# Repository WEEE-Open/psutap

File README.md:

# PSUtap
The PSUtap is a battery powered device designed to sit between the PSU (power supply unit) and the motherboard of a desktop computer.  
It's purpose is to constantly monitor the power lines (voltage and current) to detect power related issues: short circuits, open circuits, overloads, overvoltages, etc...   
It taps the lines from the main 24 pin ATX connector and the lines from another 4 pin connector to monitor:
* 12V1
* 12V2
* 5V
* 5VSB
* 3V3

## Structure of the device
The device is divided into three different boards, which are mounted on top of each other. From the bottom up, they are:
* the analog board
* the digital board
* the screen module  

The three are connected through male/female headers and communicate through an SPI interface.

## Analog board
This board gets its name from the fact that it has current sensing ICs, voltage sensing voltage dividers and an ADC to transmit the data to the digital board.  
For the current sensing, we've used some [LT6105](https://www.analog.com/media/en/technical-documentation/data-sheets/6105fa.pdf) ICs, which are essentially (differential) voltage controlled current sources. The configuration in our board is not much different than the typical application shown in the schematic.  
For the voltage sensing, we've used some regular voltage dividers, with a bit of margin so that we can also detect overvoltages.  
The ADC is an [AD7708](https://www.analog.com/media/en/technical-documentation/data-sheets/AD7708_7718.pdf), which is a delta-sigma, 16 bits, 10 channels ADC with integrated SPI interface, which is why we chose it, so that we could easily connect it to a uC without using too many wires.

## Digital Board
This board contains the uC, the brain of the entire device, a [CH340G](https://cdn.sparkfun.com/datasheets/Dev/Arduino/Other/CH340DS1.PDF) USB to serial converter,  the battery charging and protection circuit, a USB port and some buttons for the user input.  
The used uC is an [ATmega328P](https://ww1.microchip.com/downloads/en/DeviceDoc/Atmel-7810-Automotive-Microcontrollers-ATmega328P_Datasheet.pdf), which will be flashed with the Arduino bootloader so that it can be easily programmed through the Arduino IDE.  
Its main tasks are:
* reading the data coming from the ADC
* displaying on the screen
* handling user inputs
* interact with the computer through the USB port (data logging/remote control)

## Screen module
The screen module is a 240x320 2.8'' LCD, and the serial number is `tjctm24028-spi`.  
It's purpose is to show the user all the measured voltages and currents at once, so that a problem related with the power lines can be located very quickly, and also graph the voltages and currents wrt time.

## Current state
* The schematic for the analog and the digital board have been finished
* The PCB of the first board has to be redesigned completly
* The PCB of the second board has to be designed from scratch
* All the software for the microcontroller has to be written
* Testing (a lot of testing)

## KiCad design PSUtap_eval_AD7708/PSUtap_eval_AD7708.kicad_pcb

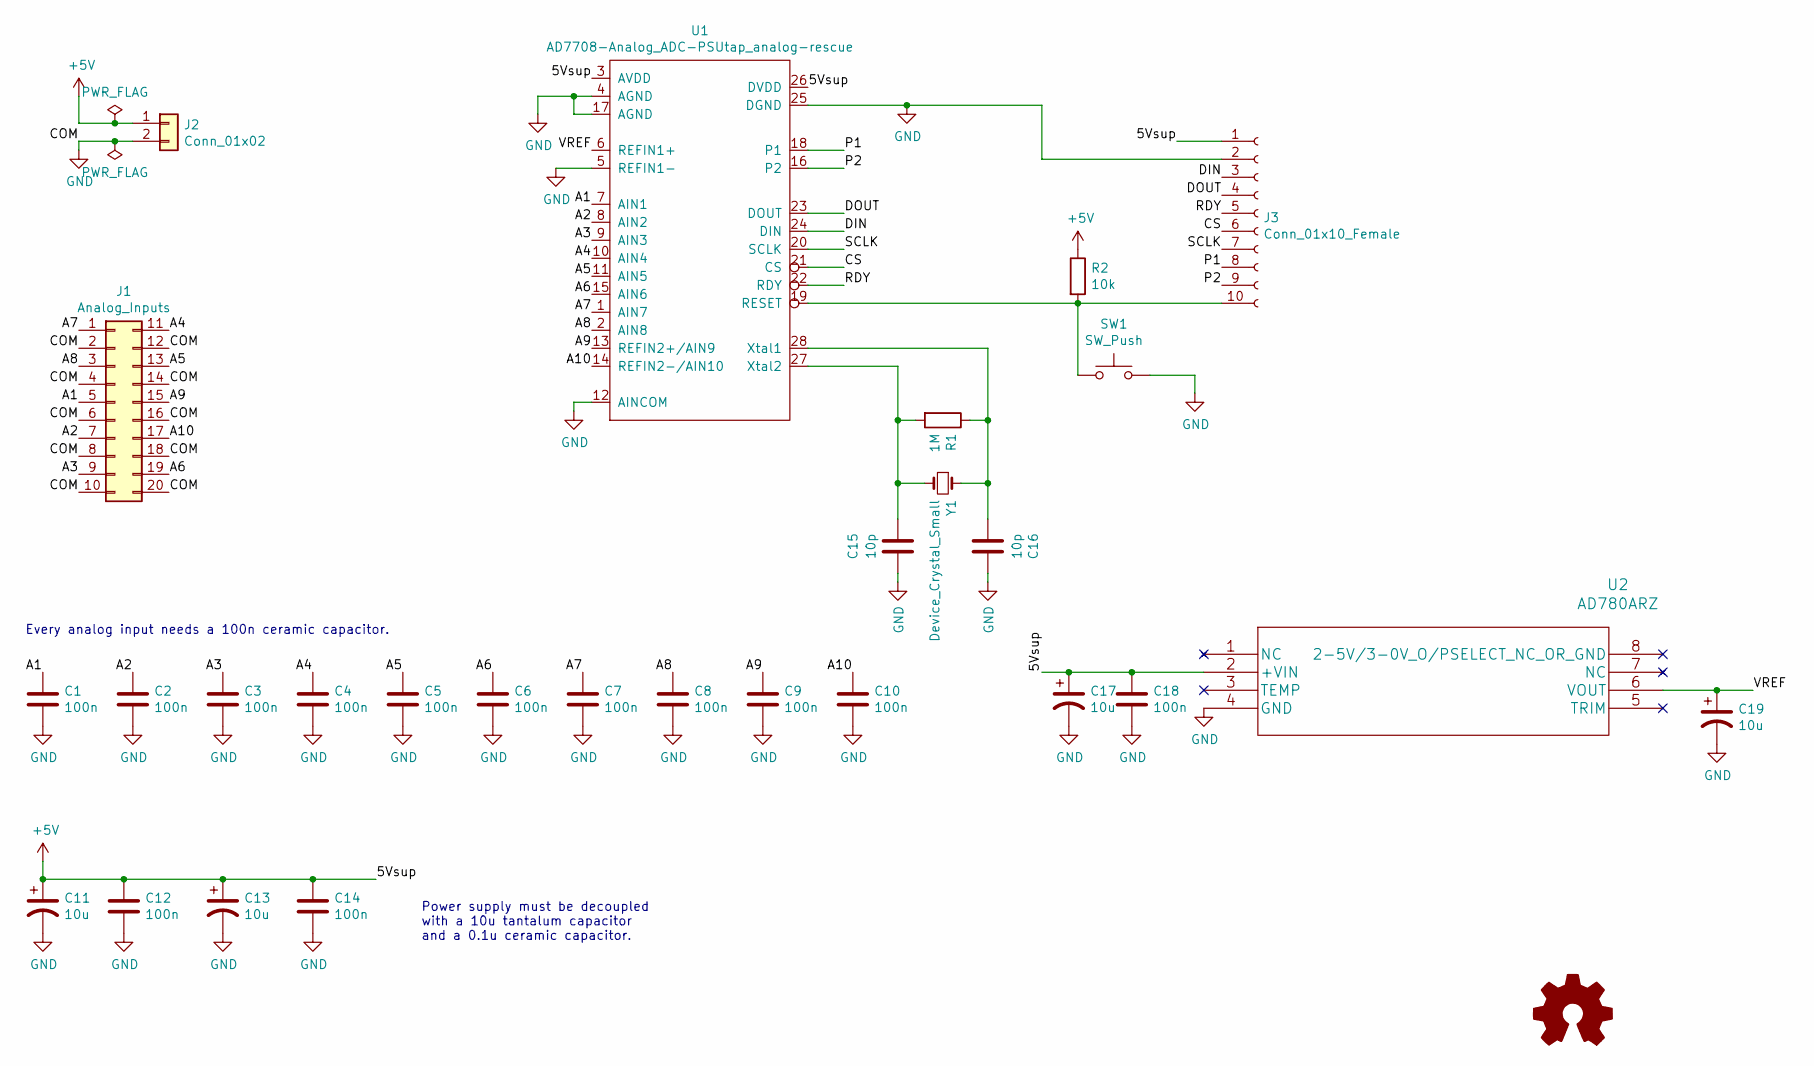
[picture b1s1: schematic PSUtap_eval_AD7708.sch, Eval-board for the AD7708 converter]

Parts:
C1, C2, C3, C4, C5, C6, C7, C8, C9, C10, C12, C14, C18: 100n; C_0603_1608Metric_Pad1.05x0.95mm_HandSolder
C11, C13, C17, C19: 10u; C_0805_2012Metric
C15, C16: 10p; C_0603_1608Metric_Pad1.05x0.95mm_HandSolder
J1: Analog_Inputs; PinSocket_2x10_P2.54mm_Vertical
J2: Conn_01x02; PinSocket_1x02_P2.54mm_Vertical
J3: Conn_01x10_Female; PinSocket_1x10_P2.54mm_Vertical
R1: 1M; R_0603_1608Metric_Pad1.05x0.95mm_HandSolder
R2: 10k; R_0603_1608Metric_Pad1.05x0.95mm_HandSolder
SW1: SW_Push; SW_SPST_B3U-1000P
U1: AD7708-Analog_ADC-PSUtap_analog-rescue; SOIC-28W_7.5x18.7mm_P1.27mm
U2: AD780ARZ; SSOP-8_3.9x5.05mm_P1.27mm
Y1: Device_Crystal_Small; Crystal_SMD_EuroQuartz_EQ161-2Pin_3.2x1.5mm_HandSoldering

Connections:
+5V: C11.1, C12.1, C13.1, C14.1, C17.1, C18.1, J2.1, J3.1, R2.1, U1.3 (AVDD), U1.26 (DVDD), U2.2 (+VIN)
/A1: C1.1, J1.5, U1.7 (AIN1)
/A2: C2.1, J1.7, U1.8 (AIN2)
/A3: C3.1, J1.9, U1.9 (AIN3)
/A4: C4.1, J1.11, U1.10 (AIN4)
/A5: C5.1, J1.13, U1.11 (AIN5)
/A6: C6.1, J1.19, U1.15 (AIN6)
/A7: C7.1, J1.1, U1.1 (AIN7)
/A8: C8.1, J1.3, U1.2 (AIN8)
/A9: C9.1, J1.15, U1.13 (REFIN2+/AIN9)
/A10: C10.1, J1.17, U1.14 (REFIN2-/AIN10)
/CS: J3.6, U1.21 (CS)
/DIN: J3.3, U1.24 (DIN)
/DOUT: J3.4, U1.23 (DOUT)
/P1: J3.8, U1.18 (P1)
/P2: J3.9, U1.16 (P2)
/RDY: J3.5, U1.22 (RDY)
/SCLK: J3.7, U1.20 (SCLK)
/VREF: C19.1, U1.6 (REFIN1+), U2.6 (VOUT); also elsewhere on the board
GND: C1.2, C2.2, C3.2, C4.2, C5.2, C6.2, C7.2, C8.2, C9.2, C10.2, C11.2, C12.2, C13.2, C14.2, C15.1, C16.1, C17.2, C18.2, C19.2, J1.2, J1.4, J1.6, J1.8, J1.10, J1.12, J1.14, J1.16, J1.18, J1.20, J2.2, J3.2, SW1.2, U1.4 (AGND), U1.5 (REFIN1-), U1.12 (AINCOM), U1.17 (AGND), U1.25 (DGND), U2.4 (GND)
unnamed: C15.2, R1.2, U1.27 (Xtal2), Y1.2
unnamed: C16.2, R1.1, U1.28 (Xtal1), Y1.1
unnamed: J3.10, R2.2, SW1.1, U1.19 (RESET)

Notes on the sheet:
Power supply must be decoupled with a 10u tantalum capacitor and a 0.1u ceramic capacitor.
Every analog input needs a 100n ceramic capacitor.

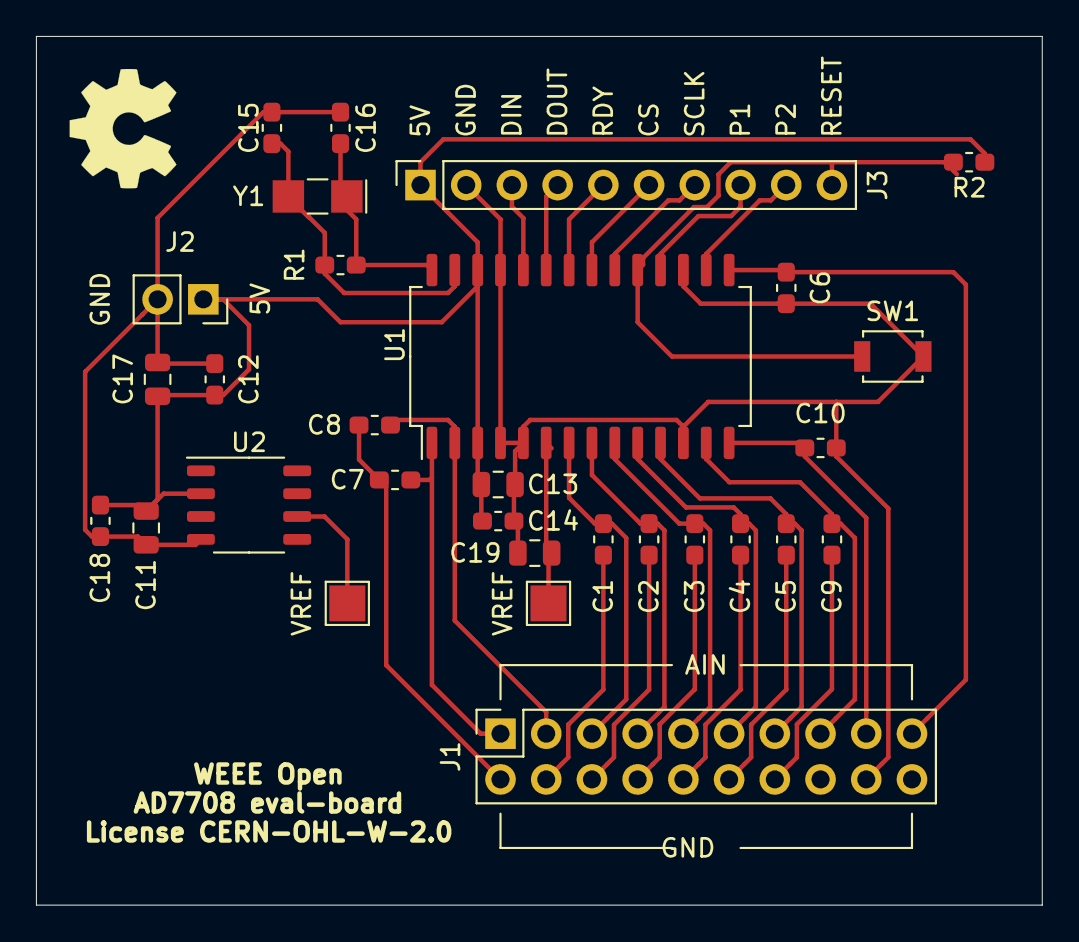
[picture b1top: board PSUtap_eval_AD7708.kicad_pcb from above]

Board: 2 copper layers, 55.9 x 48.3 mm, 30 parts (0 on the bottom side), 23 nets.

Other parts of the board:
VREF: TestPoint_Pad_2.0x2.0mm
VREF#2: TestPoint_Pad_2.0x2.0mm

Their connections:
/VREF: VREF.1, VREF#2.1; also elsewhere on the board

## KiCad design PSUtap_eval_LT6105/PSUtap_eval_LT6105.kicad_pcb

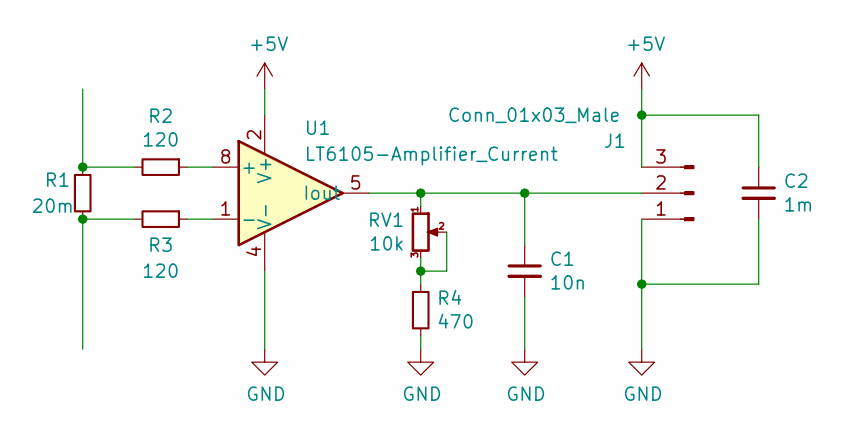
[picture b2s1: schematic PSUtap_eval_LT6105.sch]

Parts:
C1: 10n; C_0805_2012Metric_Pad1.18x1.45mm_HandSolder
C2: 1m; C_0805_2012Metric_Pad1.18x1.45mm_HandSolder
J1: Conn_01x03_Male; PinHeader_1x03_P2.54mm_Vertical
R1: 20m; R_2512_6332Metric_Pad1.40x3.35mm_HandSolder
R2, R3: 120; R_0805_2012Metric_Pad1.20x1.40mm_HandSolder
R4: 470; R_0805_2012Metric_Pad1.20x1.40mm_HandSolder
RV1: 10k; Potentiometer_Bourns_3296W_Vertical
U1: LT6105-Amplifier_Current; MSOP-8_3x3mm_P0.65mm

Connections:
+5V: C2.1, J1.3, U1.2 (V+)
GND: C1.2, C2.2, J1.1, R4.2, U1.4 (V-)
unnamed: C1.1, J1.2, RV1.1, U1.5 (Iout)
unnamed: R1.1, R2.2
unnamed: R1.2, R3.2
unnamed: R2.1, U1.8 (+)
unnamed: R3.1, U1.1 (-)
unnamed: R4.1, RV1.2, RV1.3

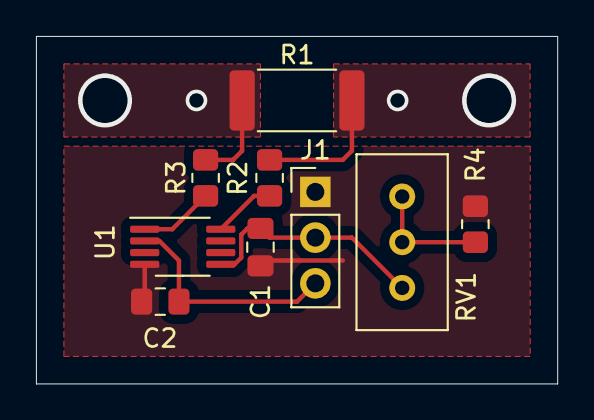
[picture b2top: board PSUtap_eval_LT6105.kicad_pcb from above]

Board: 2 copper layers, 29.0 x 19.3 mm, 9 parts (0 on the bottom side), 8 nets.

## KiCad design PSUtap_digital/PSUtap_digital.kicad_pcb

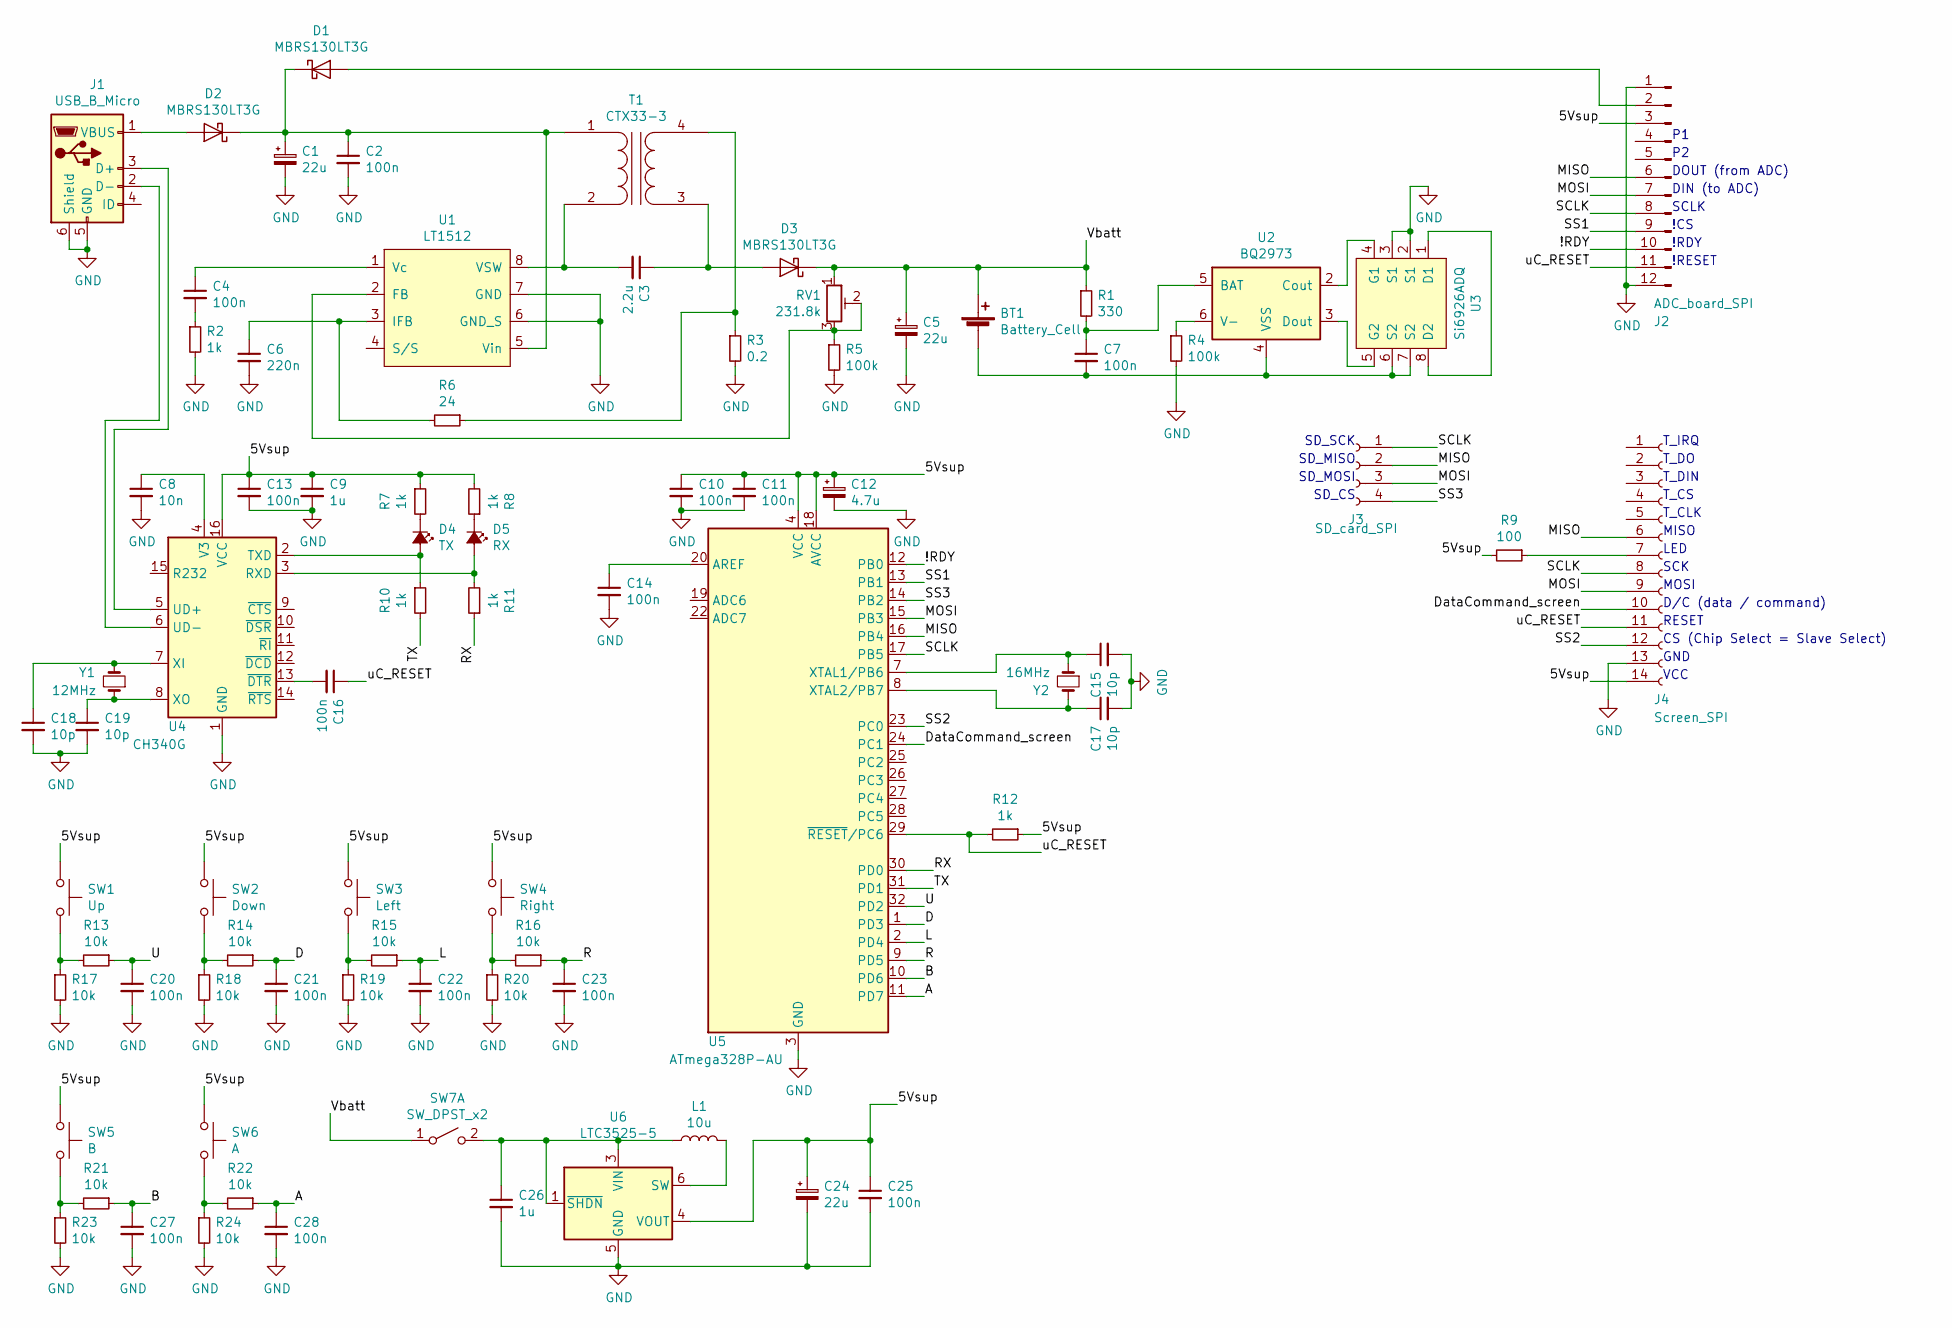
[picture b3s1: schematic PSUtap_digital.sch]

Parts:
BT1: Battery_Cell; PinHeader_1x02_P2.54mm_Vertical
C1, C5: 22u; C_0805_2012Metric_Pad1.15x1.40mm_HandSolder
C2, C4, C7, C10, C11, C13, C14, C16, C20, C21, C22, C23, C25, C27, C28: 100n; C_0603_1608Metric_Pad1.05x0.95mm_HandSolder
C3: 2.2u; C_0603_1608Metric_Pad1.05x0.95mm_HandSolder
C6: 220n; C_0603_1608Metric_Pad1.05x0.95mm_HandSolder
C8: 10n; C_0603_1608Metric_Pad1.05x0.95mm_HandSolder
C9, C26: 1u; C_0603_1608Metric_Pad1.05x0.95mm_HandSolder
C12: 4.7u; C_0603_1608Metric_Pad1.05x0.95mm_HandSolder
C15, C17, C18, C19: 10p; C_0603_1608Metric_Pad1.05x0.95mm_HandSolder
C24: 22u; C_0603_1608Metric_Pad1.05x0.95mm_HandSolder
D1, D2, D3: MBRS130LT3G; D_SMB_Handsoldering
D4: TX; D_0603_1608Metric_Pad1.05x0.95mm_HandSolder
D5: RX; D_0603_1608Metric_Pad1.05x0.95mm_HandSolder
J1: USB_B_Micro; USB_Micro-B_Molex-105017-0001
J2: ADC_board_SPI; PinHeader_1x12_P2.54mm_Vertical
J3: SD_card_SPI; PinHeader_1x04_P2.54mm_Vertical
J4: Screen_SPI; PinHeader_1x14_P2.54mm_Vertical
L1: 10u; L_Wuerth_MAPI-3012
R1: 330; R_0603_1608Metric_Pad1.05x0.95mm_HandSolder
R2, R7, R8, R10, R11, R12: 1k; R_0603_1608Metric_Pad1.05x0.95mm_HandSolder
R3: 0.2; R_0603_1608Metric_Pad1.05x0.95mm_HandSolder
R4, R5: 100k; R_0603_1608Metric_Pad1.05x0.95mm_HandSolder
R6: 24; R_0603_1608Metric_Pad1.05x0.95mm_HandSolder
R9: 100; R_0603_1608Metric_Pad1.05x0.95mm_HandSolder
R13, R14, R15, R16, R17, R18, R19, R20, R21, R22, R23, R24: 10k; R_0603_1608Metric_Pad1.05x0.95mm_HandSolder
RV1: 231.8k; TRIM_3362P-1-304
SW1: Up; SW_PUSH_6mm
SW2: Down; SW_PUSH_6mm
SW3: Left; SW_PUSH_6mm
SW4: Right; SW_PUSH_6mm
SW5: B; SW_PUSH_6mm
SW6: A; SW_PUSH_6mm
SW7: SW_DPST_x2; PinHeader_1x05_P2.00mm_Vertical
T1: CTX33-3; IND_CTX33-3-R
U1: LT1512; SO-8_3.9x4.9mm_P1.27mm
U2: BQ2973; WSON-6_1.5x1.5mm_P0.5mm
U3: Si6926ADQ; TSSOP-8_4.4x3mm_P0.65mm
U4: CH340G; SOIC-16_3.9x9.9mm_P1.27mm
U5: ATmega328P-AU; TQFP-32_7x7mm_P0.8mm
U6: LTC3525-5; SOT-363_SC-70-6
Y1: 12MHz; Crystal_SMD_5032-2Pin_5.0x3.2mm
Y2: 16MHz; Crystal_SMD_5032-2Pin_5.0x3.2mm

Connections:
/5Vsup: C9.1, C10.1, C11.1, C12.1, C13.1, C24.1, C25.1, J2.3, J4.14, R7.1, R8.2, R9.2, R12.1, SW1.1, SW2.1, SW3.1, SW4.1, SW5.1, SW6.1, U4.16 (VCC), U5.4 (VCC), U5.6 (VCC), U5.18 (AVCC), U6.4 (VOUT)
/!RDY: J2.10, U5.12 (PB0)
/A: C28.1, R22.1, U5.11 (PD7)
/B: C27.1, R21.1, U5.10 (PD6)
/D: C21.1, R14.1, U5.1 (PD3)
/DataCommand_screen: J4.10, U5.24 (PC1)
/L: C22.1, R15.1, U5.2 (PD4)
/MISO: J2.6, J3.2, J4.6, U5.16 (PB4)
/MOSI: J2.7, J3.3, J4.9, U5.15 (PB3)
/R: C23.1, R16.1, U5.9 (PD5)
/RX: R11.1, U5.30 (PD0)
/SCLK: J2.8, J3.1, J4.8, U5.17 (PB5)
/SS1: J2.9, U5.13 (PB1)
/SS2: J4.12, U5.23 (PC0)
/SS3: J3.4, U5.14 (PB2)
/TX: R10.2, U5.31 (PD1)
/U: C20.1, R13.1, U5.32 (PD2)
/uC_RESET: C16.1, J2.11, J4.11, R12.2, U5.29 (~RESET~/PC6)
GND: C1.2, C2.2, C5.2, C6.2, C8.2, C9.2, C10.2, C11.2, C12.2, C13.2, C14.2, C15.2, C17.2, C18.2, C19.2, C20.2, C21.2, C22.2, C23.2, C24.2, C25.2, C26.2, C27.2, C28.2, J1.5 (GND), J1.6 (Shield), J2.1, J2.12, J4.13, R2.2, R3.2, R4.2, R5.2, R17.2, R18.2, R19.2, R20.2, R23.2, R24.2, U1.6 (GND_S), U1.7 (GND), U3.2 (S1), U3.3 (S1), U4.1 (GND), U5.3 (GND), U5.5 (GND), U5.21 (GND), U6.2 (GND), U6.5 (GND)
unnamed: BT1.2 (-), C7.2, U2.4 (VSS), U3.6 (S2), U3.7 (S2)
unnamed: C1.1, C2.1, D1.1 (K), D2.1 (K), T1.1 (AA), U1.5 (Vin)
unnamed: C3.1, D3.2 (A), T1.3 (SA)
unnamed: C3.2, T1.2 (AB), U1.8 (VSW)
unnamed: C4.1, U1.1 (Vc)
unnamed: C4.2, R2.1
unnamed: C6.1, R6.2, U1.3 (IFB)
unnamed: C7.1, R1.2, U2.5 (BAT)
unnamed: C8.1, U4.4 (V3)
unnamed: C14.1, U5.20 (AREF)
unnamed: C15.1, U5.7 (XTAL1/PB6), Y2.1
unnamed: C16.2, U4.13 (~DTR)
unnamed: C17.1, U5.8 (XTAL2/PB7), Y2.2
unnamed: C18.1, U4.7 (XI), Y1.2
unnamed: C19.1, U4.8 (XO), Y1.1
unnamed: D1.2 (A), J2.2
unnamed: D2.2 (A), J1.1 (VBUS)
unnamed: D4.1 (K), R7.2
unnamed: D4.2 (A), R10.1, U4.2 (TXD)
unnamed: D5.1 (K), R8.1
unnamed: D5.2 (A), R11.2, U4.3 (RXD)
unnamed: J1.2 (D-), U4.6 (UD-)
unnamed: J1.3 (D+), U4.5 (UD+)
unnamed: J4.7, R9.1
unnamed: L1.2, U6.6 (SW)
unnamed: R3.1, R6.1, T1.4 (SB)
unnamed: R4.1, U2.6 (V-)
unnamed: R5.1, RV1.2, RV1.3, U1.2 (FB)
unnamed: R13.2, R17.1, SW1.2
unnamed: R14.2, R18.1, SW2.2
unnamed: R15.2, R19.1, SW3.2
unnamed: R16.2, R20.1, SW4.2
unnamed: R21.2, R23.1, SW5.2
unnamed: R22.2, R24.1, SW6.2
unnamed: U2.2 (Cout), U3.4 (G1)
unnamed: U2.3 (Dout), U3.5 (G2)
unnamed: U3.1 (D1), U3.8 (D2)

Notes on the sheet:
DOUT (from ADC)
DIN (to ADC)
SCLK
!CS
!RDY
!RESET
T_IRQ
T_DO
T_DIN
T_CS
T_CLK
MISO
LED
SCK
MOSI
D/C (data / command)
RESET
CS (Chip Select = Slave Select)
GND
VCC
SD_SCK
SD_MISO
SD_MOSI
SD_CS

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
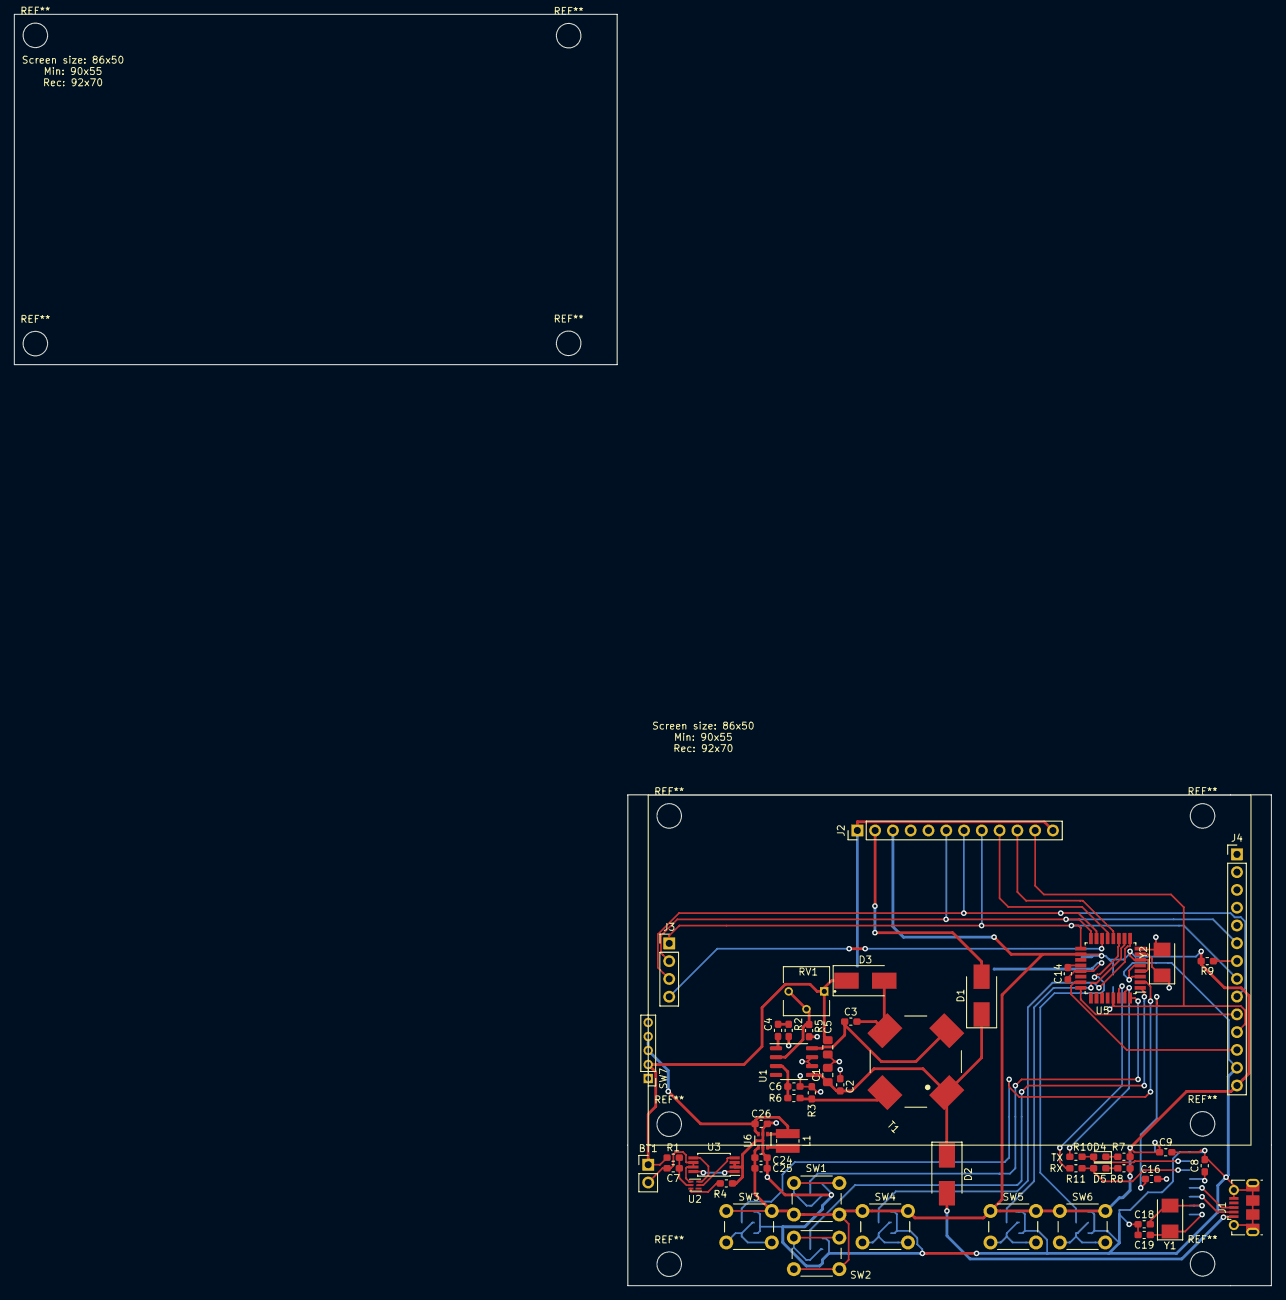
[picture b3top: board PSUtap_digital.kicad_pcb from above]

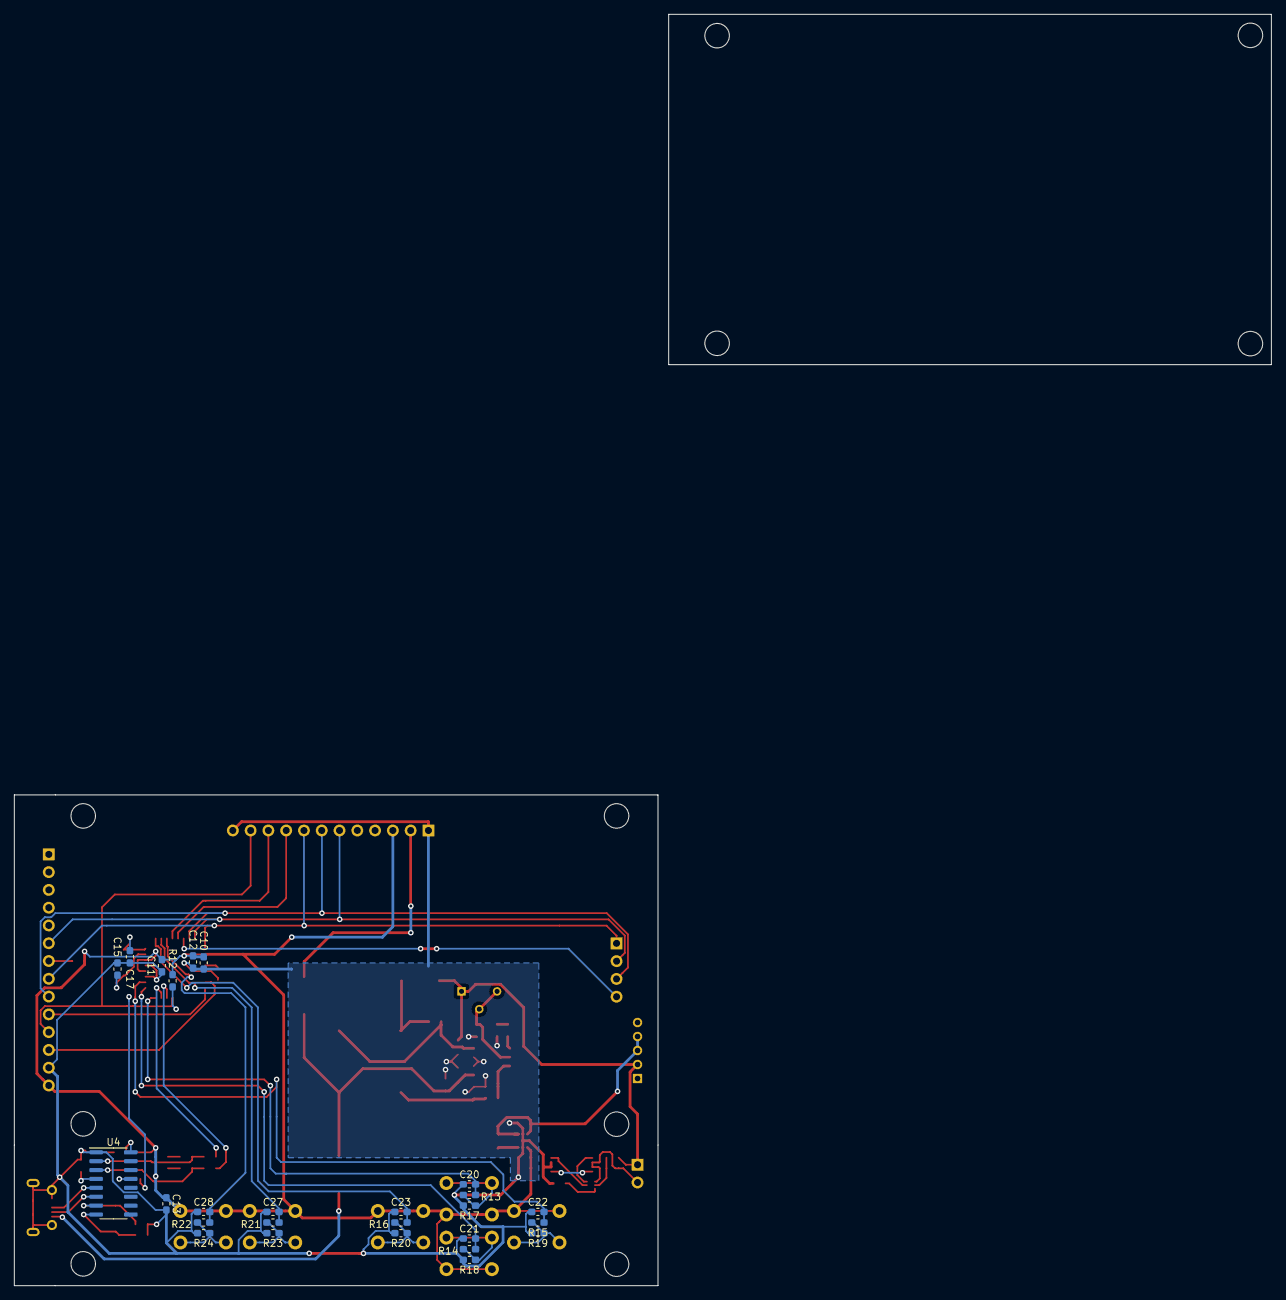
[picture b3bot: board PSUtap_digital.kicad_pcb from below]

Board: 2 copper layers, 179.6 x 181.6 mm, 80 parts (26 on the bottom side), 58 nets.

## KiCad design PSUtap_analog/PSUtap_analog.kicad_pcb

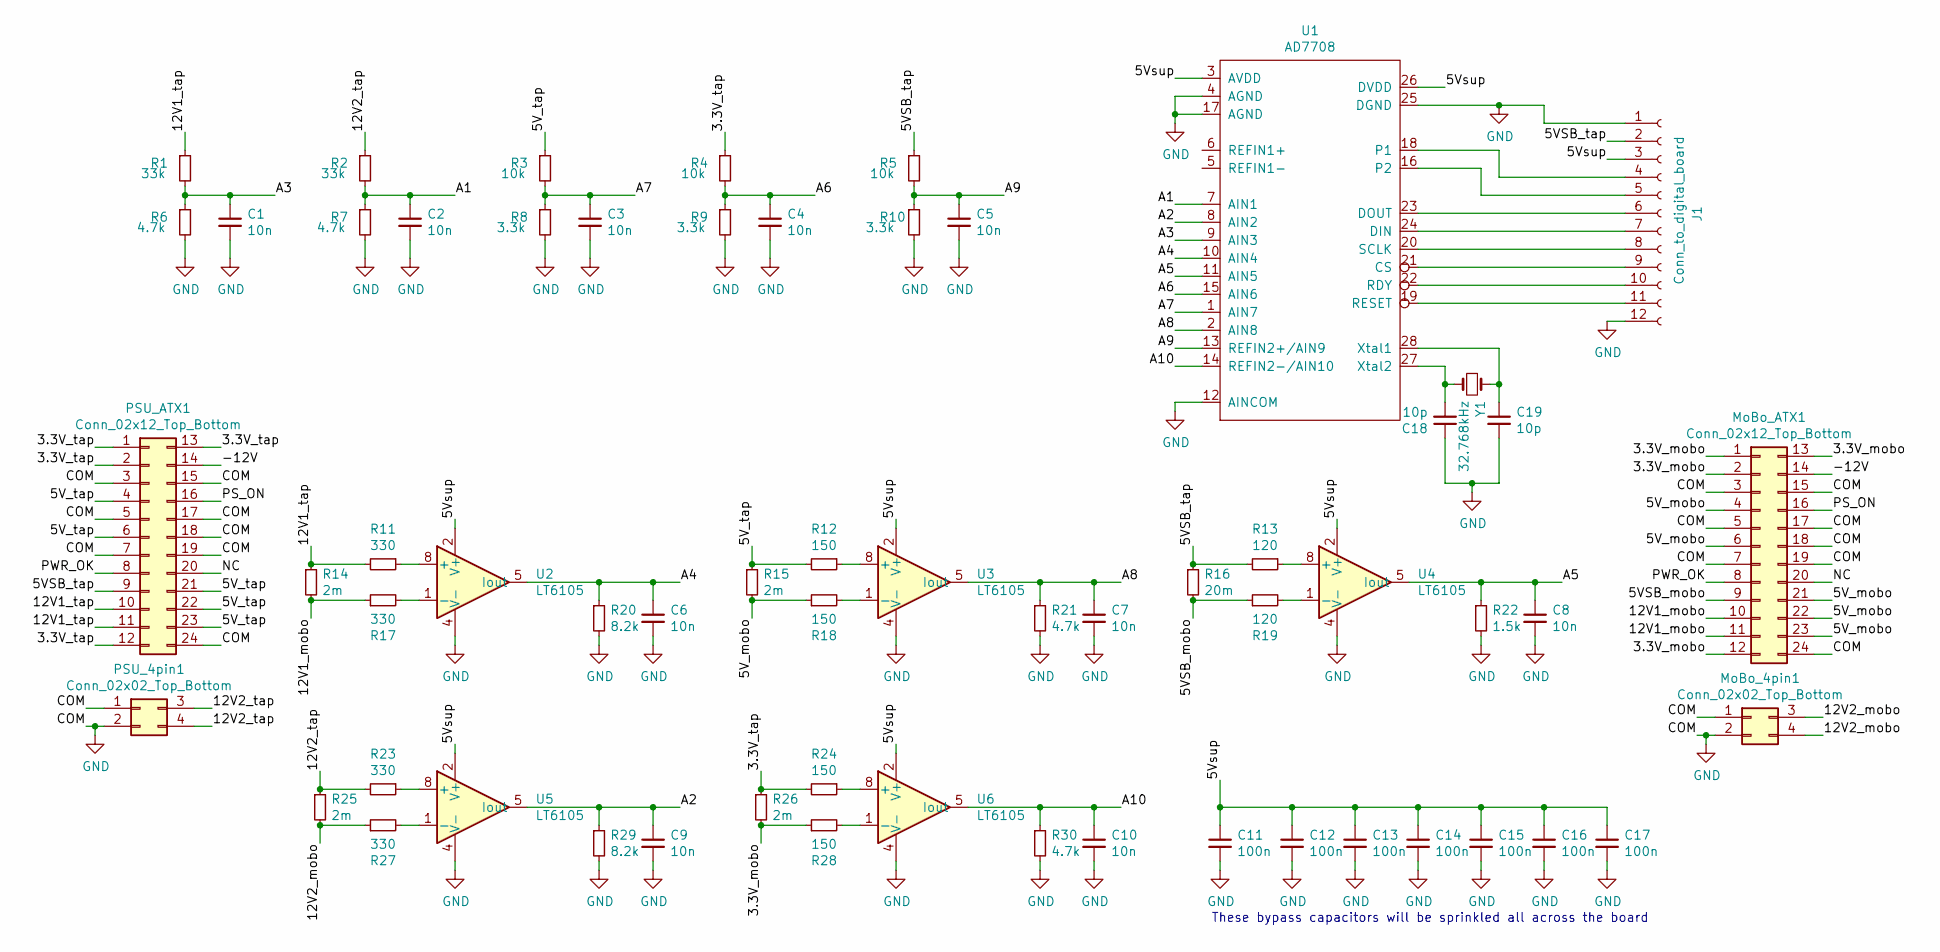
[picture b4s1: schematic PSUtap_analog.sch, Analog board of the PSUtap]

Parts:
C1, C2, C3, C4, C5, C6, C7, C8, C9, C10: 10n; C_0603_1608Metric_Pad1.05x0.95mm_HandSolder
C11, C12, C13, C14, C15, C16, C17: 100n; C_0603_1608Metric_Pad1.05x0.95mm_HandSolder
C18, C19: 10p; C_0603_1608Metric_Pad1.05x0.95mm_HandSolder
J1: Conn_to_digital_board; PinSocket_1x12_P2.54mm_Vertical
MoBo_4pin1: Conn_02x02_Top_Bottom; Molex_Mini-Fit_Jr_5566-04A_2x02_P4.20mm_Vertical
MoBo_ATX1: Conn_02x12_Top_Bottom; Molex_Mini-Fit_Jr_5566-24A_2x12_P4.20mm_Vertical
PSU_4pin1: Conn_02x02_Top_Bottom; Molex_Mini-Fit_Jr_5566-04A_2x02_P4.20mm_Vertical
PSU_ATX1: Conn_02x12_Top_Bottom; Molex_Mini-Fit_Jr_5566-24A_2x12_P4.20mm_Vertical
R1, R2: 33k; R_0603_1608Metric_Pad1.05x0.95mm_HandSolder
R3, R4, R5: 10k; R_0603_1608Metric_Pad1.05x0.95mm_HandSolder
R6, R7, R21, R30: 4.7k; R_0603_1608Metric_Pad1.05x0.95mm_HandSolder
R8, R9, R10: 3.3k; R_0603_1608Metric_Pad1.05x0.95mm_HandSolder
R11, R17, R23, R27: 330; R_0603_1608Metric_Pad1.05x0.95mm_HandSolder
R12, R18, R24, R28: 150; R_0603_1608Metric_Pad1.05x0.95mm_HandSolder
R13, R19: 120; R_0603_1608Metric_Pad1.05x0.95mm_HandSolder
R14, R15, R25, R26: 2m; R_2512_6332Metric_Pad1.52x3.35mm_HandSolder
R16: 20m; R_0805_2012Metric_Pad1.15x1.40mm_HandSolder
R20, R29: 8.2k; R_0603_1608Metric_Pad1.05x0.95mm_HandSolder
R22: 1.5k; R_0603_1608Metric_Pad1.05x0.95mm_HandSolder
U1: AD7708; SOIC-28W_7.5x18.7mm_P1.27mm
U2, U3, U4, U5, U6: LT6105; MSOP-8_3x3mm_P0.65mm
Y1: 32.768kHz; Crystal_SMD_EuroQuartz_EQ161-2Pin_3.2x1.5mm_HandSoldering

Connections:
/3.3V_mobo: MoBo_ATX1.1, MoBo_ATX1.2, MoBo_ATX1.12, MoBo_ATX1.13, R26.2, R28.1
/3.3V_tap: PSU_ATX1.1, PSU_ATX1.2, PSU_ATX1.12, PSU_ATX1.13, R4.1, R24.2, R26.1
/5VSB_mobo: MoBo_ATX1.9, R16.2, R19.1
/5VSB_tap: J1.2, PSU_ATX1.9, R5.1, R13.2, R16.1
/5V_mobo: MoBo_ATX1.4, MoBo_ATX1.6, MoBo_ATX1.21, MoBo_ATX1.22, MoBo_ATX1.23, R15.2, R18.1
/5V_tap: PSU_ATX1.4, PSU_ATX1.6, PSU_ATX1.21, PSU_ATX1.22, PSU_ATX1.23, R3.1, R12.2, R15.1
/5Vsup: C11.1, C12.1, C13.1, C14.1, C15.1, C16.1, C17.1, J1.3, U1.3 (AVDD), U1.26 (DVDD), U2.2 (V+), U3.2 (V+), U4.2 (V+), U5.2 (V+), U6.2 (V+)
/12V1_mobo: MoBo_ATX1.10, MoBo_ATX1.11, R14.2, R17.1
/12V1_tap: PSU_ATX1.10, PSU_ATX1.11, R1.1, R11.2, R14.1
/12V2_mobo: MoBo_4pin1.3, MoBo_4pin1.4, R25.2, R27.1
/12V2_tap: PSU_4pin1.3, PSU_4pin1.4, R2.1, R23.2, R25.1
/-12V: MoBo_ATX1.14, PSU_ATX1.14
/A1: C2.1, R2.2, R7.1, U1.7 (AIN1)
/A2: C9.1, R29.1, U1.8 (AIN2), U5.5 (Iout)
/A3: C1.1, R1.2, R6.1, U1.9 (AIN3)
/A4: C6.1, R20.1, U1.10 (AIN4), U2.5 (Iout)
/A5: C8.1, R22.1, U1.11 (AIN5), U4.5 (Iout)
/A6: C4.1, R4.2, R9.1, U1.15 (AIN6)
/A7: C3.1, R3.2, R8.1, U1.1 (AIN7)
/A8: C7.1, R21.1, U1.2 (AIN8), U3.5 (Iout)
/A9: C5.1, R5.2, R10.1, U1.13 (REFIN2+/AIN9)
/A10: C10.1, R30.1, U1.14 (REFIN2-/AIN10), U6.5 (Iout)
/NC: MoBo_ATX1.20, PSU_ATX1.20
/PS_ON: MoBo_ATX1.16, PSU_ATX1.16
/PWR_OK: MoBo_ATX1.8, PSU_ATX1.8
GND: C1.2, C2.2, C3.2, C4.2, C5.2, C6.2, C7.2, C8.2, C9.2, C10.2, C11.2, C12.2, C13.2, C14.2, C15.2, C16.2, C17.2, C18.1, C19.2, J1.1, J1.12, MoBo_4pin1.1, MoBo_4pin1.2, MoBo_ATX1.3, MoBo_ATX1.5, MoBo_ATX1.7, MoBo_ATX1.15, MoBo_ATX1.17, MoBo_ATX1.18, MoBo_ATX1.19, MoBo_ATX1.24, PSU_4pin1.1, PSU_4pin1.2, PSU_ATX1.3, PSU_ATX1.5, PSU_ATX1.7, PSU_ATX1.15, PSU_ATX1.17, PSU_ATX1.18, PSU_ATX1.19, PSU_ATX1.24, R6.2, R7.2, R8.2, R9.2, R10.2, R20.2, R21.2, R22.2, R29.2, R30.2, U1.4 (AGND), U1.12 (AINCOM), U1.17 (AGND), U1.25 (DGND), U2.4 (V-), U3.4 (V-), U4.4 (V-), U5.4 (V-), U6.4 (V-)
unnamed: C18.2, U1.27 (Xtal2), Y1.2
unnamed: C19.1, U1.28 (Xtal1), Y1.1
unnamed: J1.4, U1.18 (P1)
unnamed: J1.5, U1.16 (P2)
unnamed: J1.6, U1.23 (DOUT)
unnamed: J1.7, U1.24 (DIN)
unnamed: J1.8, U1.20 (SCLK)
unnamed: J1.9, U1.21 (CS)
unnamed: J1.10, U1.22 (RDY)
unnamed: J1.11, U1.19 (RESET)
unnamed: R11.1, U2.8 (+)
unnamed: R12.1, U3.8 (+)
unnamed: R13.1, U4.8 (+)
unnamed: R17.2, U2.1 (-)
unnamed: R18.2, U3.1 (-)
unnamed: R19.2, U4.1 (-)
unnamed: R23.1, U5.8 (+)
unnamed: R24.1, U6.8 (+)
unnamed: R27.2, U5.1 (-)
unnamed: R28.2, U6.1 (-)

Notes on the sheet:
These bypass capacitors will be sprinkled all across the board

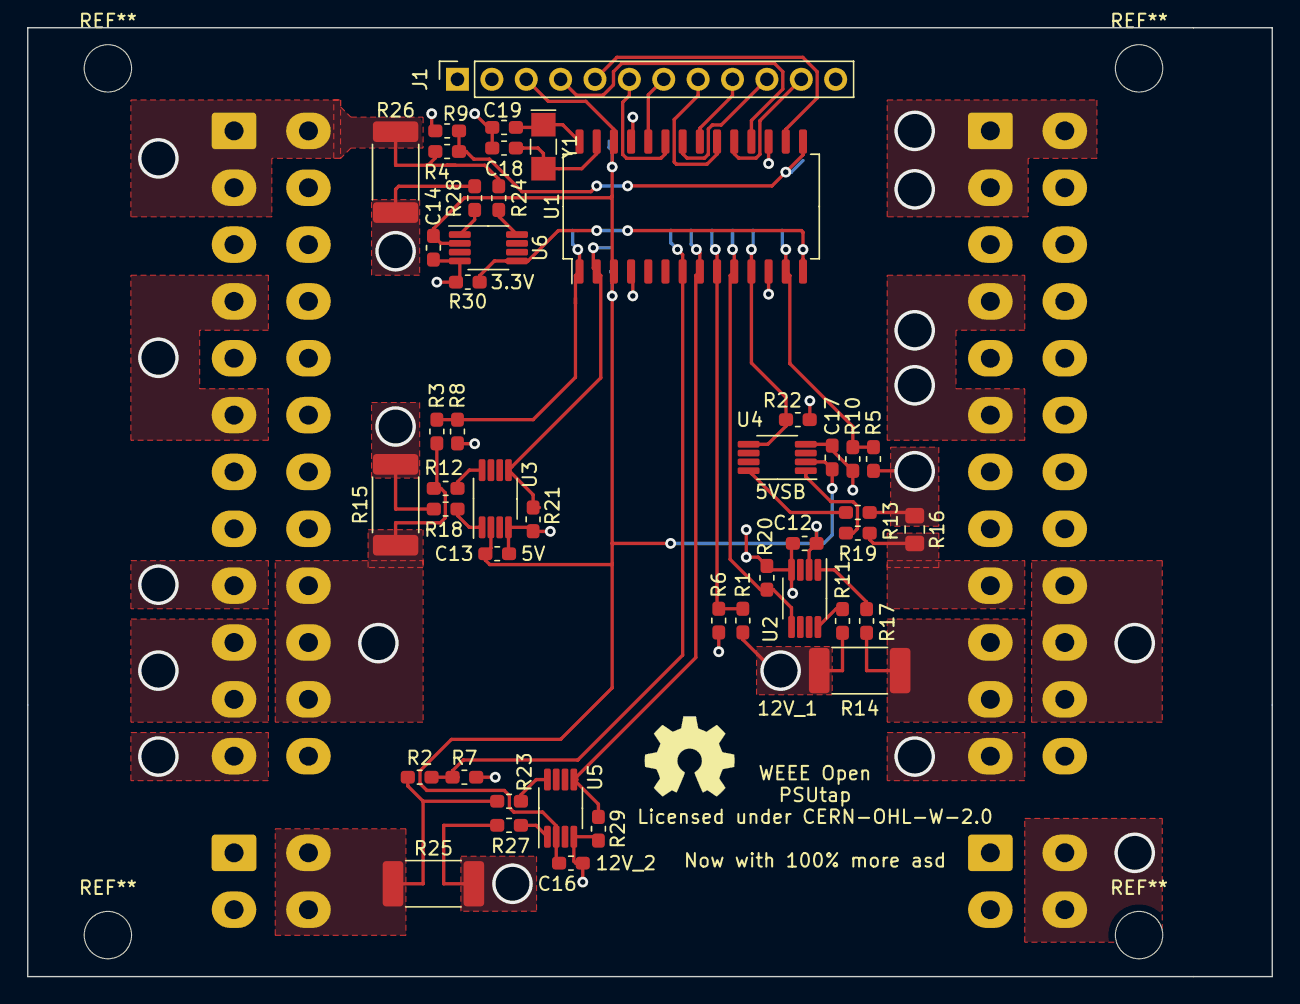
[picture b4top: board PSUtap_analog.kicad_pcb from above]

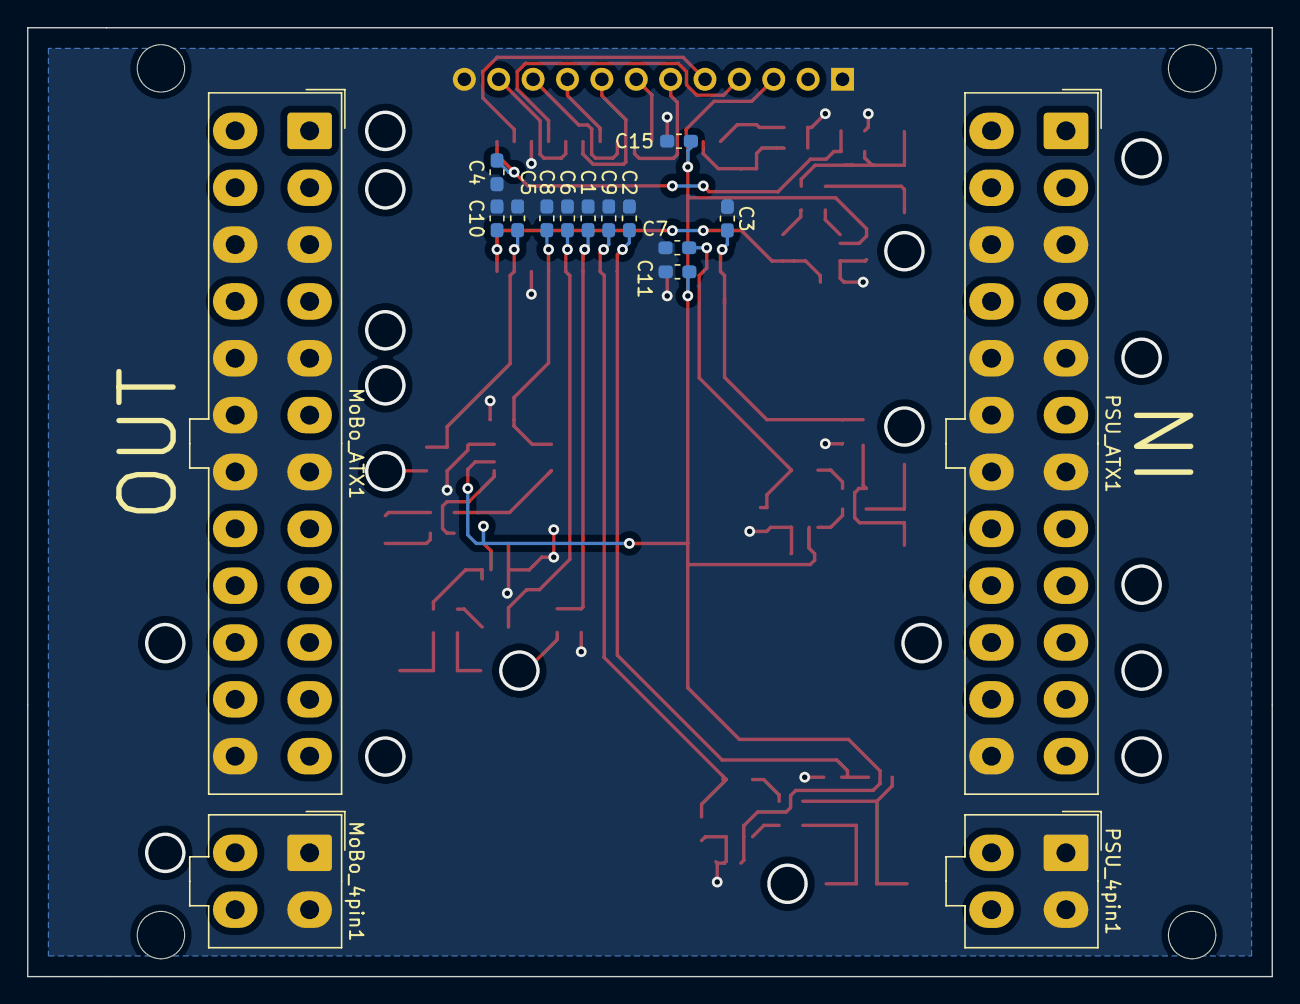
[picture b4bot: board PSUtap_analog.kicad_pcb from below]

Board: 2 copper layers, 91.9 x 70.1 mm, 61 parts (16 on the bottom side), 46 nets.

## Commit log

2020-11-01 Added all the project files
2020-11-12 Updated analog board PCB and started digital board PSB
2020-11-19 Added ATMega firmware 1.0-alpha
    + pin assignments
    + display SPI connection
    + mSD SPI connection
    + display basic info & print tests
    + mSD basic info
    + buttons press check
2020-11-19 Caching of project footprints
    KiCad "digital rescue" of externally sourced footprints into cache
2020-11-23 Fixed uSD card SDI init
2020-11-23 Fixed uSD volume info
    Now it only prints uSD volume info if it finds a volume
2020-11-28 Copied the digital PCB for parallel collaboration
2020-12-13 Removed PCB copies, added xtal to ADC in analog board, finished digital board's PCB
2021-01-06 Updated PCBs to not have vias on component pads
2021-03-06 updated fw naming scheme
    adopted a more conventional naming scheme for variables and reviewed the aesthetics of the code
2021-03-06 added vs code files to .gitignore
2021-03-06 fixed uSD volume_size declaration
2021-04-07 Update sym-lib-table
2021-04-07 added LT6105 custom symbol
2021-04-07 created evaluation board for LT6105
2021-04-07 updated project with custom library
2021-04-09 updated kicad projects caches
2021-04-09 improved buttons state array
    removed separate bools for each button, added enum for button names, consolidated button_state array throughout the code
    also slightly improved code readability
2021-04-15 created evaluation board for AD7708
2021-05-12 single-sided evaluation board for AD7708
2021-05-13 removed case notes
2021-05-13 created case bottom SW part
2021-05-14 renamed case bottom SW part file
2021-05-14 created display_board SW part
2021-09-23 Shrink AD7708 PCB
2021-09-23 style: replaced spaces with tabs
2021-09-23 add: sldprt display board pcb
2021-09-23 style: renamed display_board to display
2021-09-23 add: sldprt analog pcb
2021-09-23 style: renamed extrusion feature
2021-09-23 add: sldprt digital pcb
2021-09-28 feat: digital.sldprt U4 back PCB extr
2021-09-28 feat: analog.sldprt MOLEX pwr back PCB extr
2021-10-01 Separate WEEE and OPEN with space
2021-11-08 add: MOLEX L connectors models

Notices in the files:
PSUtap_analog/PSUtap_analog.kicad_pcb:
Licensed under CERN-OHL-W-2.0
PSUtap_eval_AD7708/PSUtap_eval_AD7708.kicad_pcb:
License CERN-OHL-W-2.0
